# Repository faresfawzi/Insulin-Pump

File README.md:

# Open Source AI-Enhanced 3D-Printed Insulin Pump
## Abstract
This research aims to develop functional 3D printed low-cost wearable insulin pumps for precise and personalized dosing for type 1 diabetes mellitus (T1DM) patients. The system utilizes artificial intelligence (AI) insulin to predict personalized bolus insulin dosages and send the dosing configuration wirelessly to an in-house developed IoT-reconfigurable pumping system to deliver the specified dosage to the patient. Historical patients’ data are fed to a cloud-based machine learning model to predict the personalized amount of bolus insulin based on the patient’s blood glucose levels, the amount of carbohydrates consumed, and physical activity. The system delivers U100 insulin bolus dosage at a flow rate of 750μl/min against an estimated 0.764 kPa backpressure produced by the patient’s subcutaneous tissue, which is 6 to 8 times faster than current insulin pumping systems. In addition to the system’s AI-enhancement, IoT connectivity, small footprint, and low power consumption, the system’s cost is predicted at under $35, making it an excellent candidate to fill a market gap and act as a fully autonomous artificial pancreas that improves the quality of life of T1DM patients.

## Citation

If you build on this project, please cite this paper.

```
@inproceedings{fawzi2023open,
  title={Open Source AI-Enhanced 3D-Printed Insulin Pump},
  author={Fawzi, Fares and Sedky, Mostafa and Abohammar, Youssef and Sharara, Hossam and Serry, Mohamed},
  booktitle={2023 IEEE Applied Sensing Conference (APSCON)},
  pages={1--4},
  year={2023},
  organization={IEEE}
}
```

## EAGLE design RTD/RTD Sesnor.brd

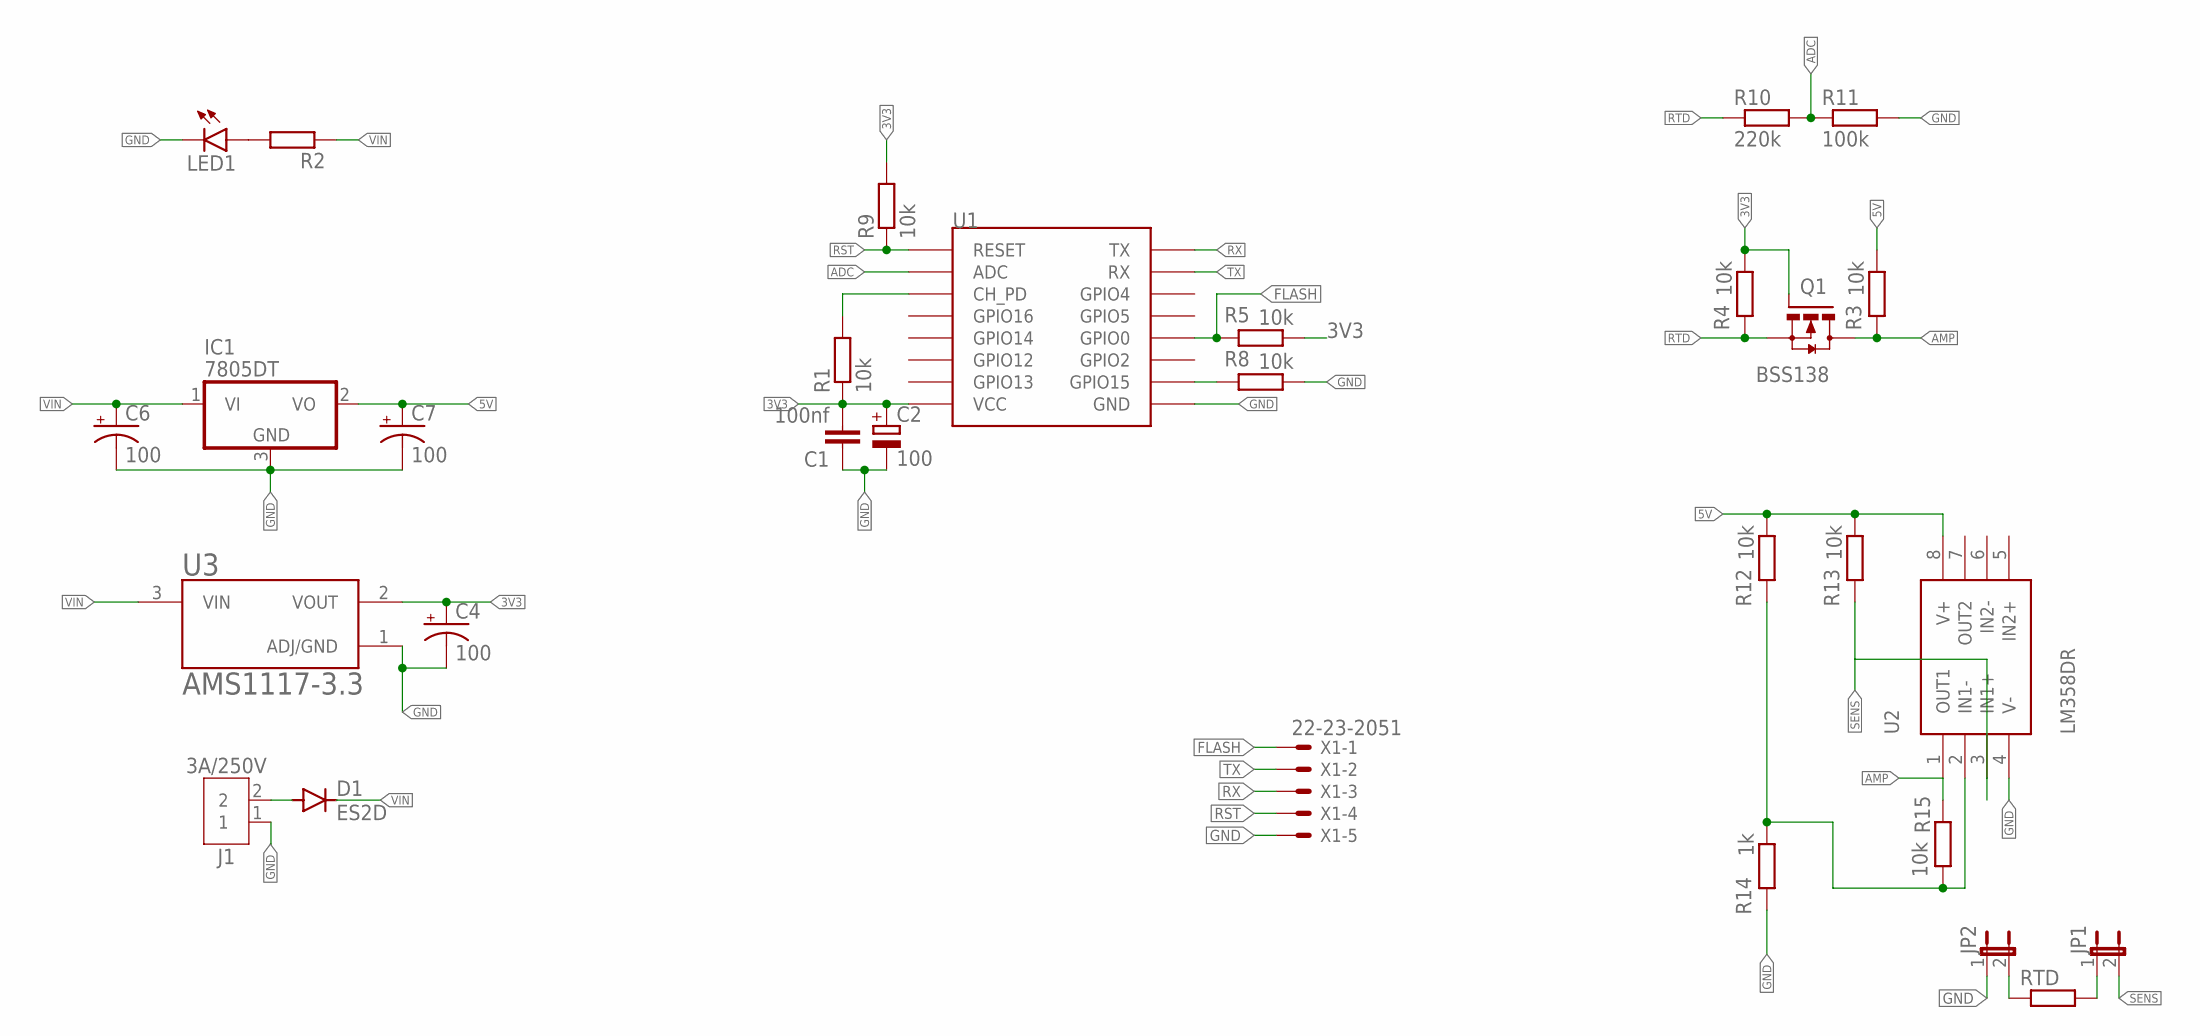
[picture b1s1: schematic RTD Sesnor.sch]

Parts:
C1: 100nf; C0805K
C2, C4, C6, C7: 100; 153CLV-0605
D1: ES2D; SMB
IC1: 7805DT; TO252
J1: 3A/250V; B2B-XH-A
JP1, JP2: JP1E; JP1
LED1: LED3MM
Q1: BSS138; SOT23-3
R1, R3, R4, R5, R8, R9, R12, R13, R15: 10k; R1206
R2: R-EU_R1206; R1206
R10: 220k; 0204/7
R11: 100k; 0204/7
R14: 1k; R1206
RTD: R-EU_M0805; M0805
U1: ESP12SMD; ESP12-SMD
U2: LM358DR
U3: AMS1117-3.3; SOT229P700X180-4N
X1: 22-23-2051

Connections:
3V3: C1.2, C2.+, C4.+, Q1.1 (G), R1.1, R4.1, R5.1, R9.2, U1.VCC, U3.2 (VOUT)
5V: C7.+, IC1.2 (VO), R3.1, R12.1, R13.1, U2.8 (V+)
ADC: R10.2, R11.1, U1.ADC
AMP: Q1.3 (D), R3.2, R15.2, U2.1 (OUT1)
FLASH: R5.2, U1.GPIO0, X1.1
GND: C1.1, C2.-, C4.-, C6.-, C7.-, IC1.3 (GND), J1.1, JP2.1, LED1.K (C), R8.1, R11.2, R14.2, U1.GND, U2.4 (V-), U3.1 (ADJ/GND), X1.5
unnamed: R1.2, U1.CH_PD
unnamed: LED1.A, R2.2
unnamed: JP2.2, RTD.1
unnamed: JP1.1, RTD.2
unnamed: R8.2, U1.GPIO15
unnamed: D1.A, J1.2
unnamed: R12.2, R14.1, R15.1, U2.2 (IN1-)
RST: R9.1, U1.RESET, X1.4
RTD: Q1.2 (S), R4.2, R10.1
RX: U1.TXD0 (TX), X1.3
SENS: JP1.2, R13.2, U2.3 (IN1+)
TX: U1.RXD0 (RX), X1.2
VIN: C6.+, D1.C, IC1.1 (VI), R2.1, U3.3 (VIN)

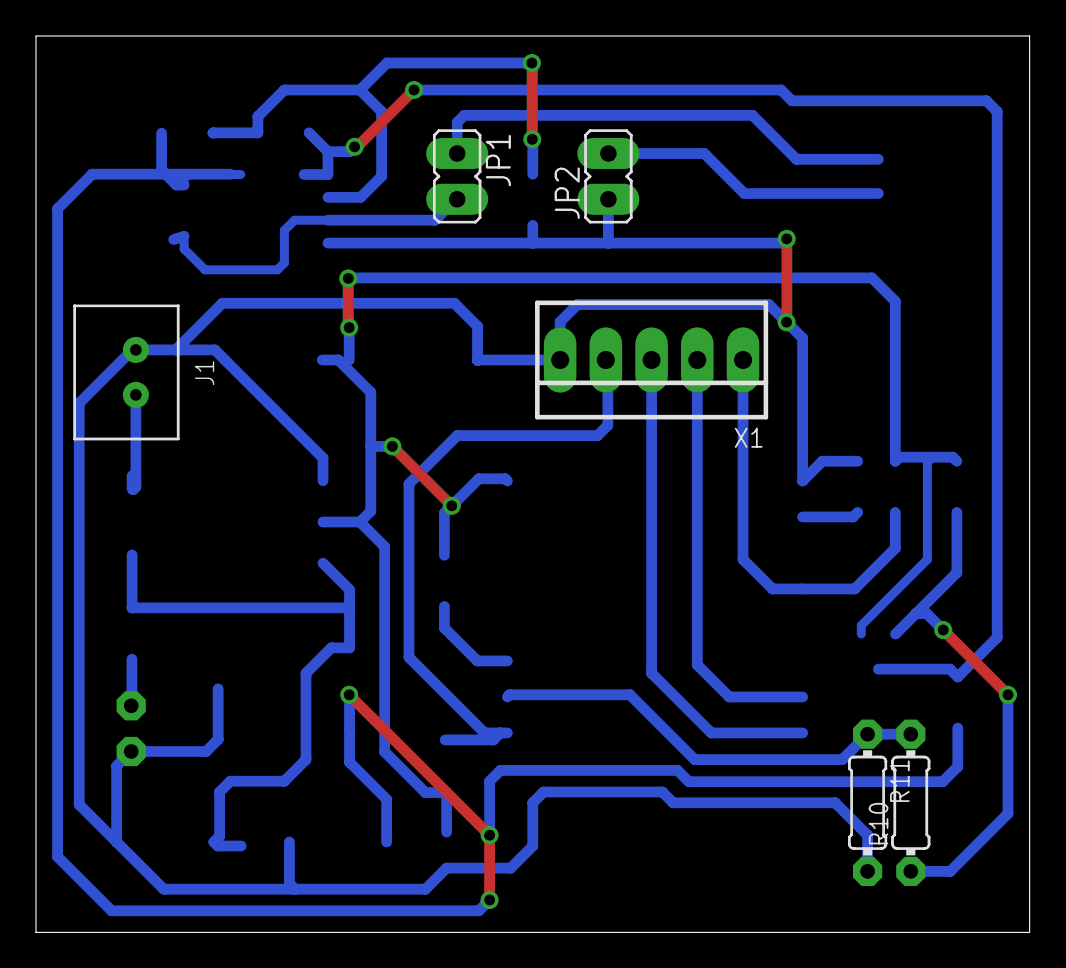
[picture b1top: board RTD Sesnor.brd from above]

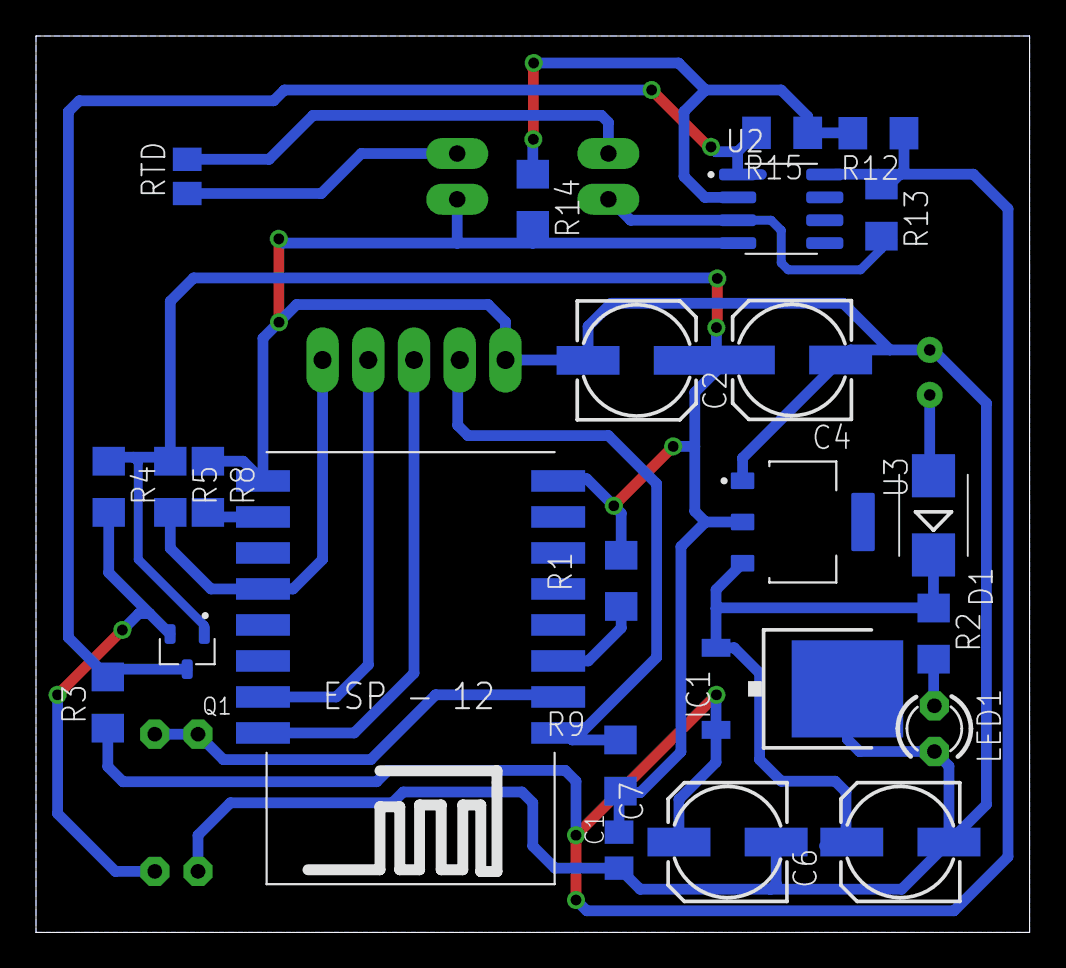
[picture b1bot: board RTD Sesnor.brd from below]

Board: 2 copper layers, 55.2 x 49.8 mm, 30 parts (24 on the bottom side), 19 nets.

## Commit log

2025-10-25 Revise project title in README
    Updated project title to reflect AI-enhanced features.
